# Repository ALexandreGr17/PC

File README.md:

# PC

Collection de fichier utiliser et d'experience sur la creation d'un PC

## Clock
Circuit représentant un module de clock utilisant de 555NE

2 mode:
    Astable avec frequence reglable (entre 7Hz et 1.44 KHz)
    Monostable

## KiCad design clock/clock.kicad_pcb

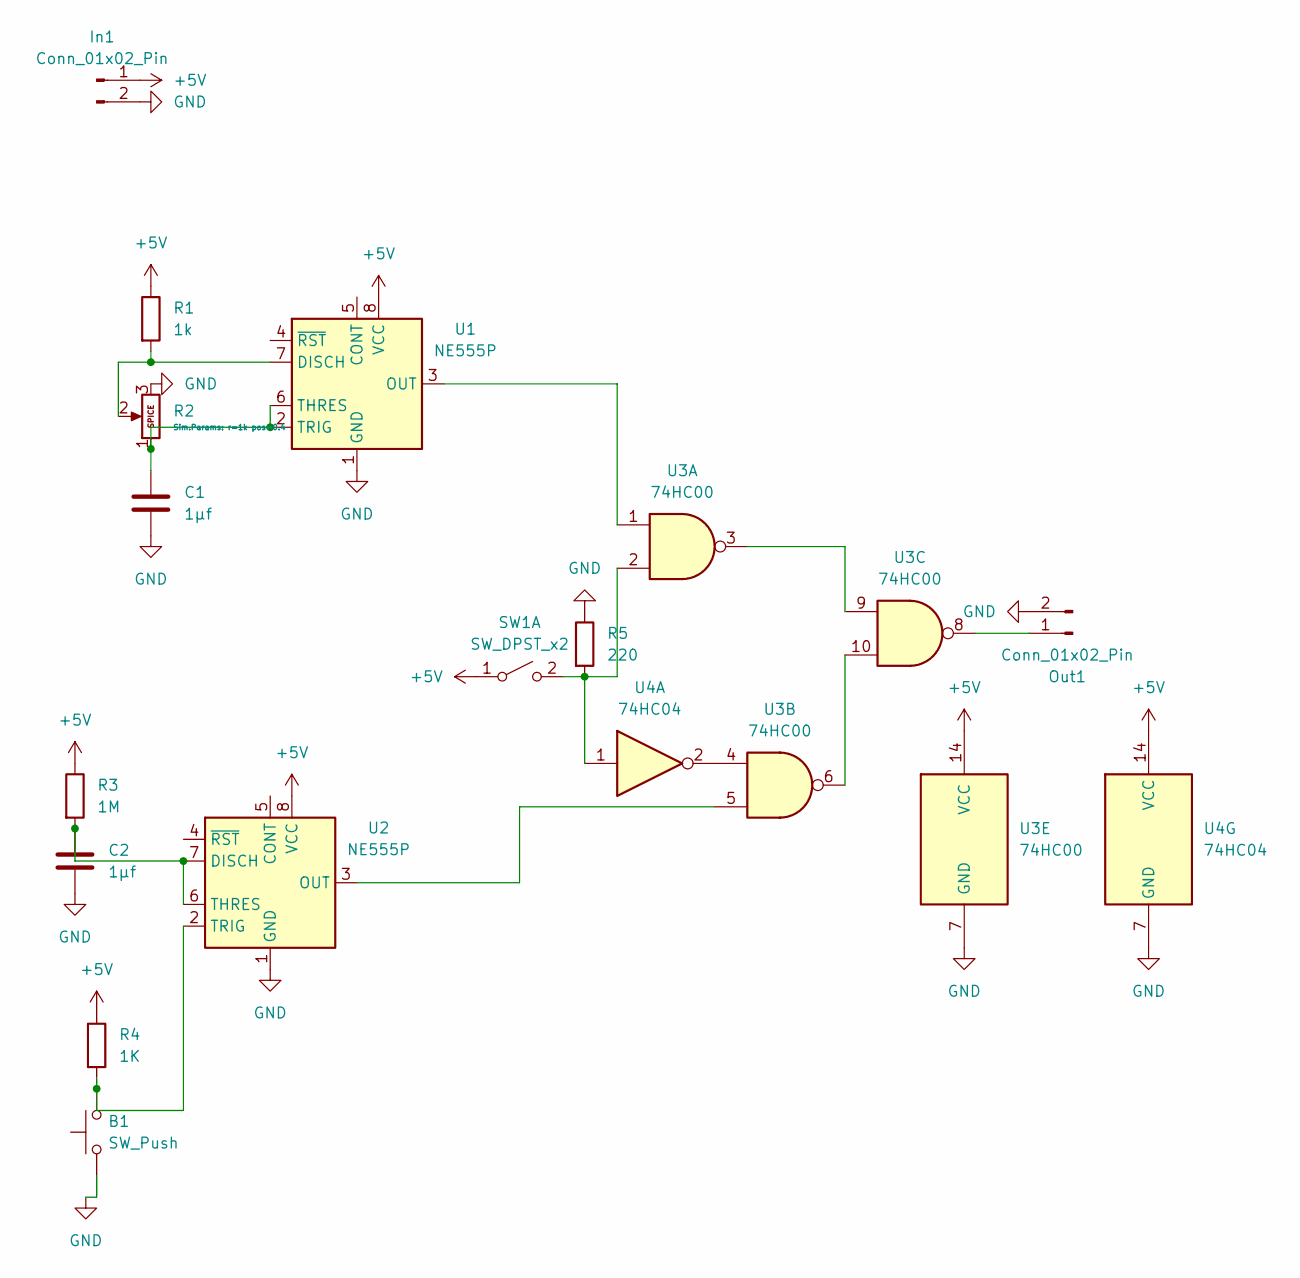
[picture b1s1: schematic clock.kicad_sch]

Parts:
B1: SW_Push; SW_PUSH_6mm
C1, C2: 1µf; CP_Radial_D5.0mm_P2.00mm
In1: Conn_01x02_Pin; PinHeader_1x02_P2.00mm_Vertical
Out1: Conn_01x02_Pin; PinHeader_1x02_P2.00mm_Vertical
R1: 1k; R_Axial_DIN0309_L9.0mm_D3.2mm_P15.24mm_Horizontal
R2: Potentiometer; Potentiometer_ACP_CA9-H2,5_Horizontal
R3: 1M; R_Axial_DIN0309_L9.0mm_D3.2mm_P15.24mm_Horizontal
R4: 1K; R_Axial_DIN0309_L9.0mm_D3.2mm_P15.24mm_Horizontal
R5: 220; R_Axial_DIN0309_L9.0mm_D3.2mm_P15.24mm_Horizontal
SW1: SW_DPST_x2; SW_DIP_SPSTx01_Slide_6.7x4.1mm_W7.62mm_P2.54mm_LowProfile
U1, U2: NE555P; DIP-8_W7.62mm
U3: 74HC00; CERDIP-14_W7.62mm_SideBrazed
U4: 74HC04; CERDIP-14_W7.62mm_SideBrazed

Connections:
+5V: In1.1, R1.1, R3.1, R4.1, SW1.1 (A), U1.8 (VCC), U2.8 (VCC), U3.14 (VCC), U4.14 (VCC)
GND: B1.1, C1.2, C2.2, In1.2, Out1.2, R2.3, R5.1, U1.1 (GND), U2.1 (GND), U3.7 (GND), U4.7 (GND)
unnamed: Out1.1, U3.8
unnamed: R5.2, SW1.2 (B), U3.2, U4.1
unnamed: R1.2, R2.2, U1.7 (DISCH)
unnamed: U1.3 (OUT), U3.1
unnamed: C1.1, R2.1, U1.2 (TRIG), U1.6 (THRES)
unnamed: C2.1, R3.2, U2.6 (THRES), U2.7 (DISCH)
unnamed: U2.3 (OUT), U3.5
unnamed: B1.2, R4.2, U2.2 (TRIG)
unnamed: U3.3, U3.9
unnamed: U3.4, U4.2
unnamed: U3.6, U3.10

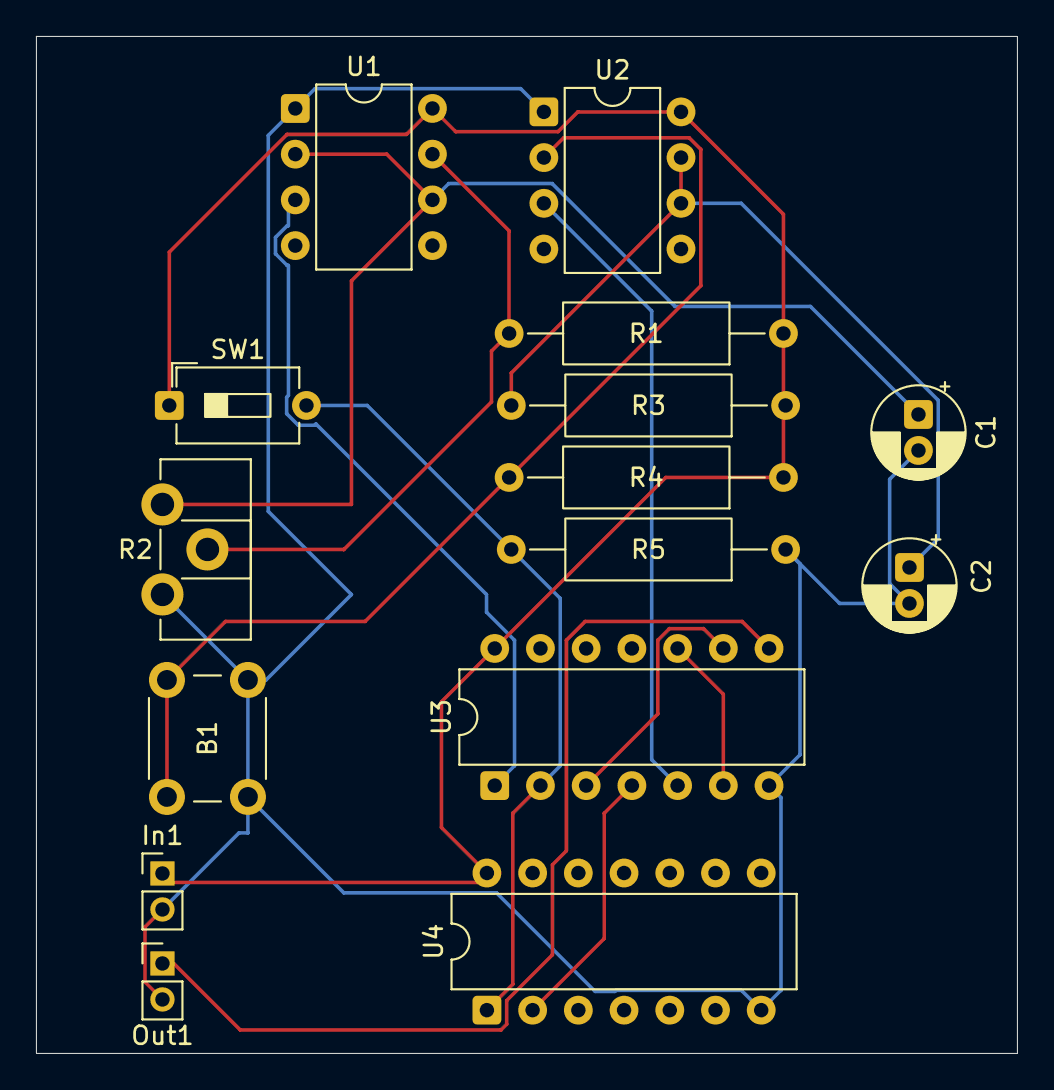
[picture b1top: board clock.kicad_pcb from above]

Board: 2 copper layers, 54.5 x 56.5 mm, 15 parts (0 on the bottom side), 13 nets.
